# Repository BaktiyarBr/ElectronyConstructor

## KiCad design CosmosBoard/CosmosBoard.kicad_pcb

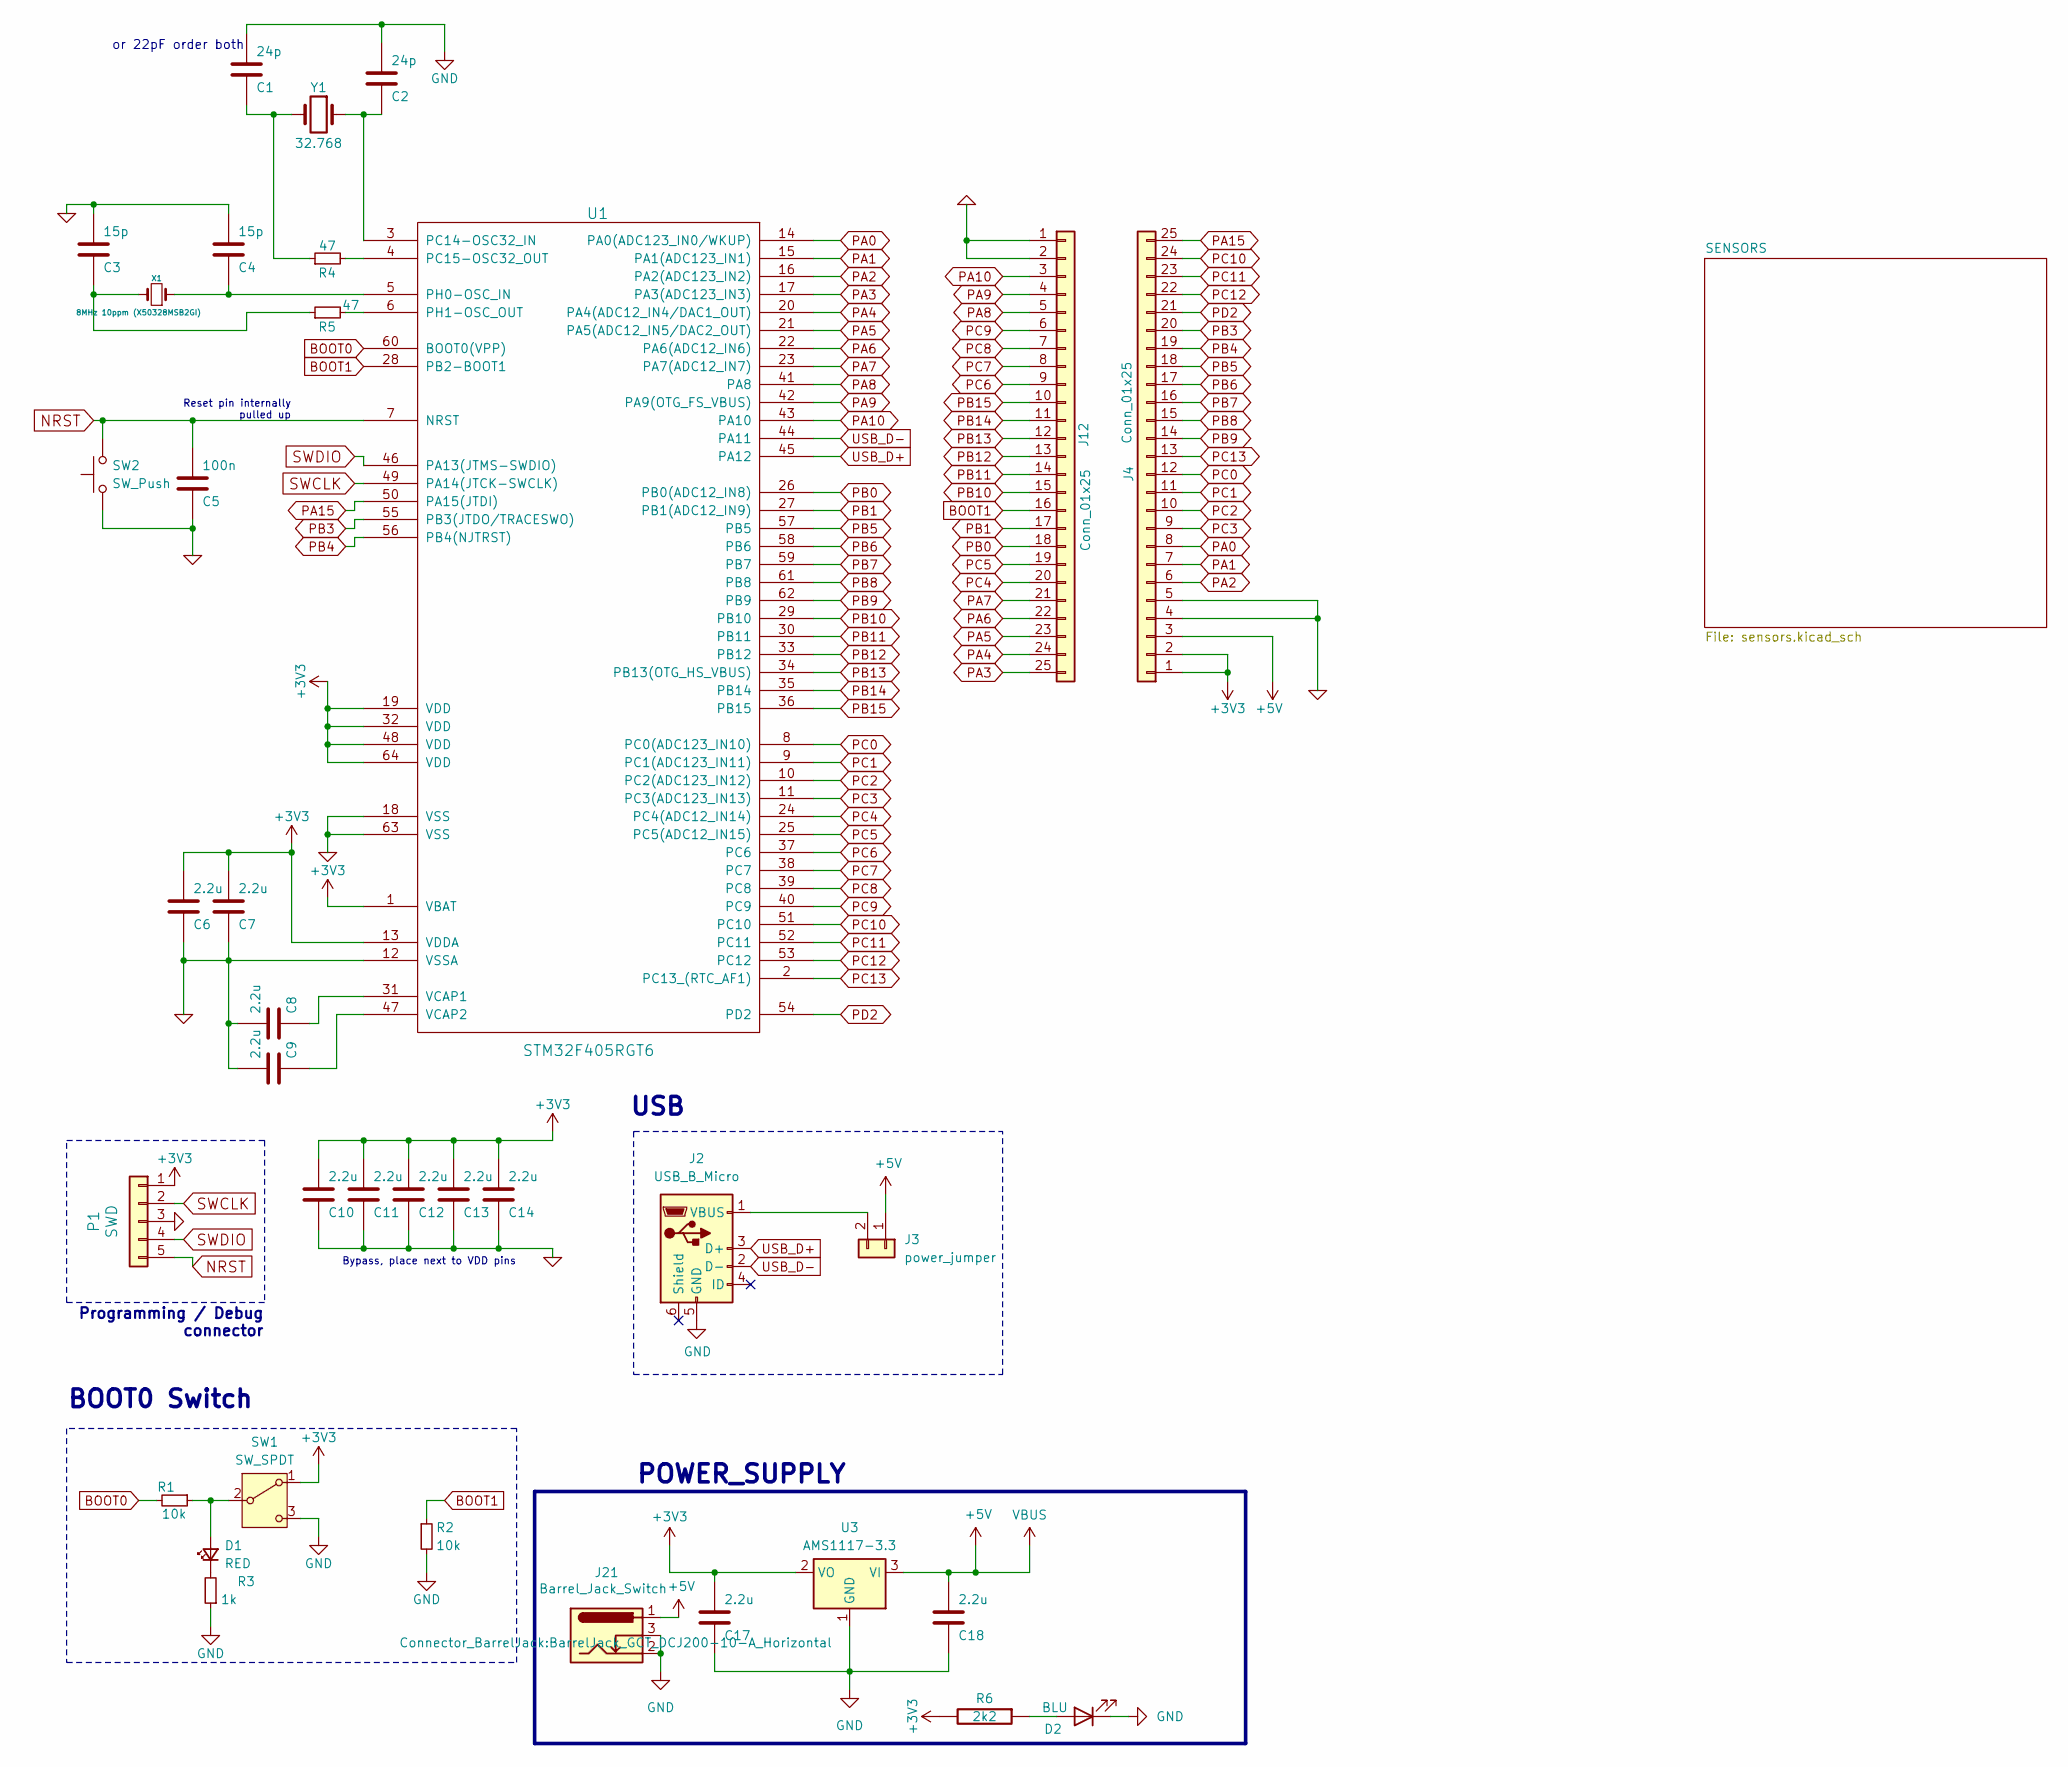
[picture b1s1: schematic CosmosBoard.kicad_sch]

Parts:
C1, C2: 24p; C_0603_1608Metric
C3, C4: 15p; C_0603_1608Metric
C5: 100n; C_0603_1608Metric
C6, C7, C8, C9, C10, C11, C12, C13, C14, C17, C18: 2.2u; C_0603_1608Metric
D1: RED; LED_0603_1608Metric; LCSC Part # C2286
D2: BLU; LED_0603_1608Metric
J2: USB_B_Micro; USB_Mini-B_Lumberg_2486_01_Horizontal
J3: power_jumper; PinHeader_1x02_P2.54mm_Vertical
J4, J12: Conn_01x25; PinHeader_1x25_P2.54mm_Vertical
J21: Barrel_Jack_Switch; BarrelJack_GCT_DCJ200-10-A_Horizontal
P1: SWD; PinHeader_1x05_P2.54mm_Vertical
R1, R2: 10k; R_0603_1608Metric_Pad0.98x0.95mm_HandSolder; LCSC Part # C25744
R3: 1k; R_0603_1608Metric_Pad0.98x0.95mm_HandSolder; LCSC Part # C21190
R4, R5: 47; R_0603_1608Metric_Pad0.98x0.95mm_HandSolder; LCSC Part # C25118
R6: 2k2; R_0603_1608Metric_Pad0.98x0.95mm_HandSolder
SW1: SW_SPDT; SW_SPDT_PCM12
SW2: SW_Push; SW_Push_SPST_NO_Alps_SKRK
U1: STM32F405RGT6; LQFP-64_10x10mm_P0.5mm
U3: AMS1117-3.3; SOT-223-3_TabPin2
X1: 8MHz 10ppm (X50328MSB2GI); Crystal_SMD_5032-2Pin_5.0x3.2mm; mfg# ABM3B-8.0-10-1UT
Y1: 32.768; Crystal_SMD_3215-2Pin_3.2x1.5mm

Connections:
+3V3: C6.2, C7.2, C10.2, C11.2, C12.2, C13.2, C14.2, C17.2, J4.1, J4.2, P1.1, R6.2, SW1.1 (A), U1.1 (VBAT), U1.13 (VDDA), U1.19 (VDD), U1.32 (VDD), U1.48 (VDD), U1.64 (VDD), U3.2 (VO); also elsewhere on the board
+5V: C18.2, J3.1, J4.3, J21.1, U3.3 (VI); also elsewhere on the board
BOOT0: R1.2, U1.60 (BOOT0(VPP))
BOOT1: J12.16, R2.1, U1.28 (PB2-BOOT1)
GND: C1.2, C2.2, C3.2, C4.2, C5.1, C6.1, C7.1, C8.2, C9.2, C10.1, C11.1, C12.1, C13.1, C14.1, C17.1, C18.1, D2.1 (K), J2.5 (GND), J4.4, J4.5, J12.1, J12.2, J21.2, J21.3, P1.3, R2.2, R3.1, SW1.3 (C), SW2.1, U1.12 (VSSA), U1.18 (VSS), U1.63 (VSS), U3.1 (GND); also elsewhere on the board
NRST: C5.2, P1.5, SW2.2, U1.7 (NRST)
unnamed: C1.1, R4.1, Y1.2
unnamed: C3.1, R5.1, X1.2
unnamed: D1.2 (A), R1.1, SW1.2 (B)
unnamed: D1.1 (K), R3.2
unnamed: D2.2 (A), R6.1
unnamed: J2.1 (VBUS), J3.2
unnamed: C2.1, U1.3 (PC14-OSC32_IN), Y1.1
unnamed: R4.2, U1.4 (PC15-OSC32_OUT)
unnamed: C4.1, U1.5 (PH0-OSC_IN), X1.1
unnamed: R5.2, U1.6 (PH1-OSC_OUT)
unnamed: C8.1, U1.31 (VCAP1)
unnamed: C9.1, U1.47 (VCAP2)
PA0: J4.8, U1.14 (PA0(ADC123_IN0/WKUP))
PA1: J4.7, U1.15 (PA1(ADC123_IN1))
PA2: J4.6, U1.16 (PA2(ADC123_IN2))
PA3: J12.25, U1.17 (PA3(ADC123_IN3))
PA4: J12.24, U1.20 (PA4(ADC12_IN4/DAC1_OUT))
PA5: J12.23, U1.21 (PA5(ADC12_IN5/DAC2_OUT))
PA6: J12.22, U1.22 (PA6(ADC12_IN6))
PA7: J12.21, U1.23 (PA7(ADC12_IN7))
PA8: J12.5, U1.41 (PA8)
PA9: J12.4, U1.42 (PA9(OTG_FS_VBUS))
PA10: J12.3, U1.43 (PA10)
PA15: J4.25, U1.50 (PA15(JTDI))
PB0: J12.18, U1.26 (PB0(ADC12_IN8))
PB1: J12.17, U1.27 (PB1(ADC12_IN9))
PB3: J4.20, U1.55 (PB3(JTDO/TRACESWO))
PB4: J4.19, U1.56 (PB4(NJTRST))
PB5: J4.18, U1.57 (PB5)
PB6: J4.17, U1.58 (PB6)
PB7: J4.16, U1.59 (PB7)
PB8: J4.15, U1.61 (PB8)
PB9: J4.14, U1.62 (PB9)
PB10: J12.15, U1.29 (PB10)
PB11: J12.14, U1.30 (PB11)
PB12: J12.13, U1.33 (PB12)
PB13: J12.12, U1.34 (PB13(OTG_HS_VBUS))
PB14: J12.11, U1.35 (PB14)
PB15: J12.10, U1.36 (PB15)
PC0: J4.12, U1.8 (PC0(ADC123_IN10))
PC1: J4.11, U1.9 (PC1(ADC123_IN11))
PC2: J4.10, U1.10 (PC2(ADC123_IN12))
PC3: J4.9, U1.11 (PC3(ADC123_IN13))
PC4: J12.20, U1.24 (PC4(ADC12_IN14))
PC5: J12.19, U1.25 (PC5(ADC12_IN15))
PC6: J12.9, U1.37 (PC6)
PC7: J12.8, U1.38 (PC7)
PC8: J12.7, U1.39 (PC8)
PC9: J12.6, U1.40 (PC9)
PC10: J4.24, U1.51 (PC10)
PC11: J4.23, U1.52 (PC11)
PC12: J4.22, U1.53 (PC12)
PC13: J4.13, U1.2 (PC13_(RTC_AF1))
PD2: J4.21, U1.54 (PD2)
SWCLK: P1.2, U1.49 (PA14(JTCK-SWCLK))
SWDIO: P1.4, U1.46 (PA13(JTMS-SWDIO))
USB_D+: J2.3 (D+), U1.45 (PA12)
USB_D-: J2.2 (D-), U1.44 (PA11)

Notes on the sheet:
USB
POWER_SUPPLY
BOOT0 Switch
Reset pin internally pulled up
Programming / Debug connector
Bypass, place next to VDD pins
or 22pF order both

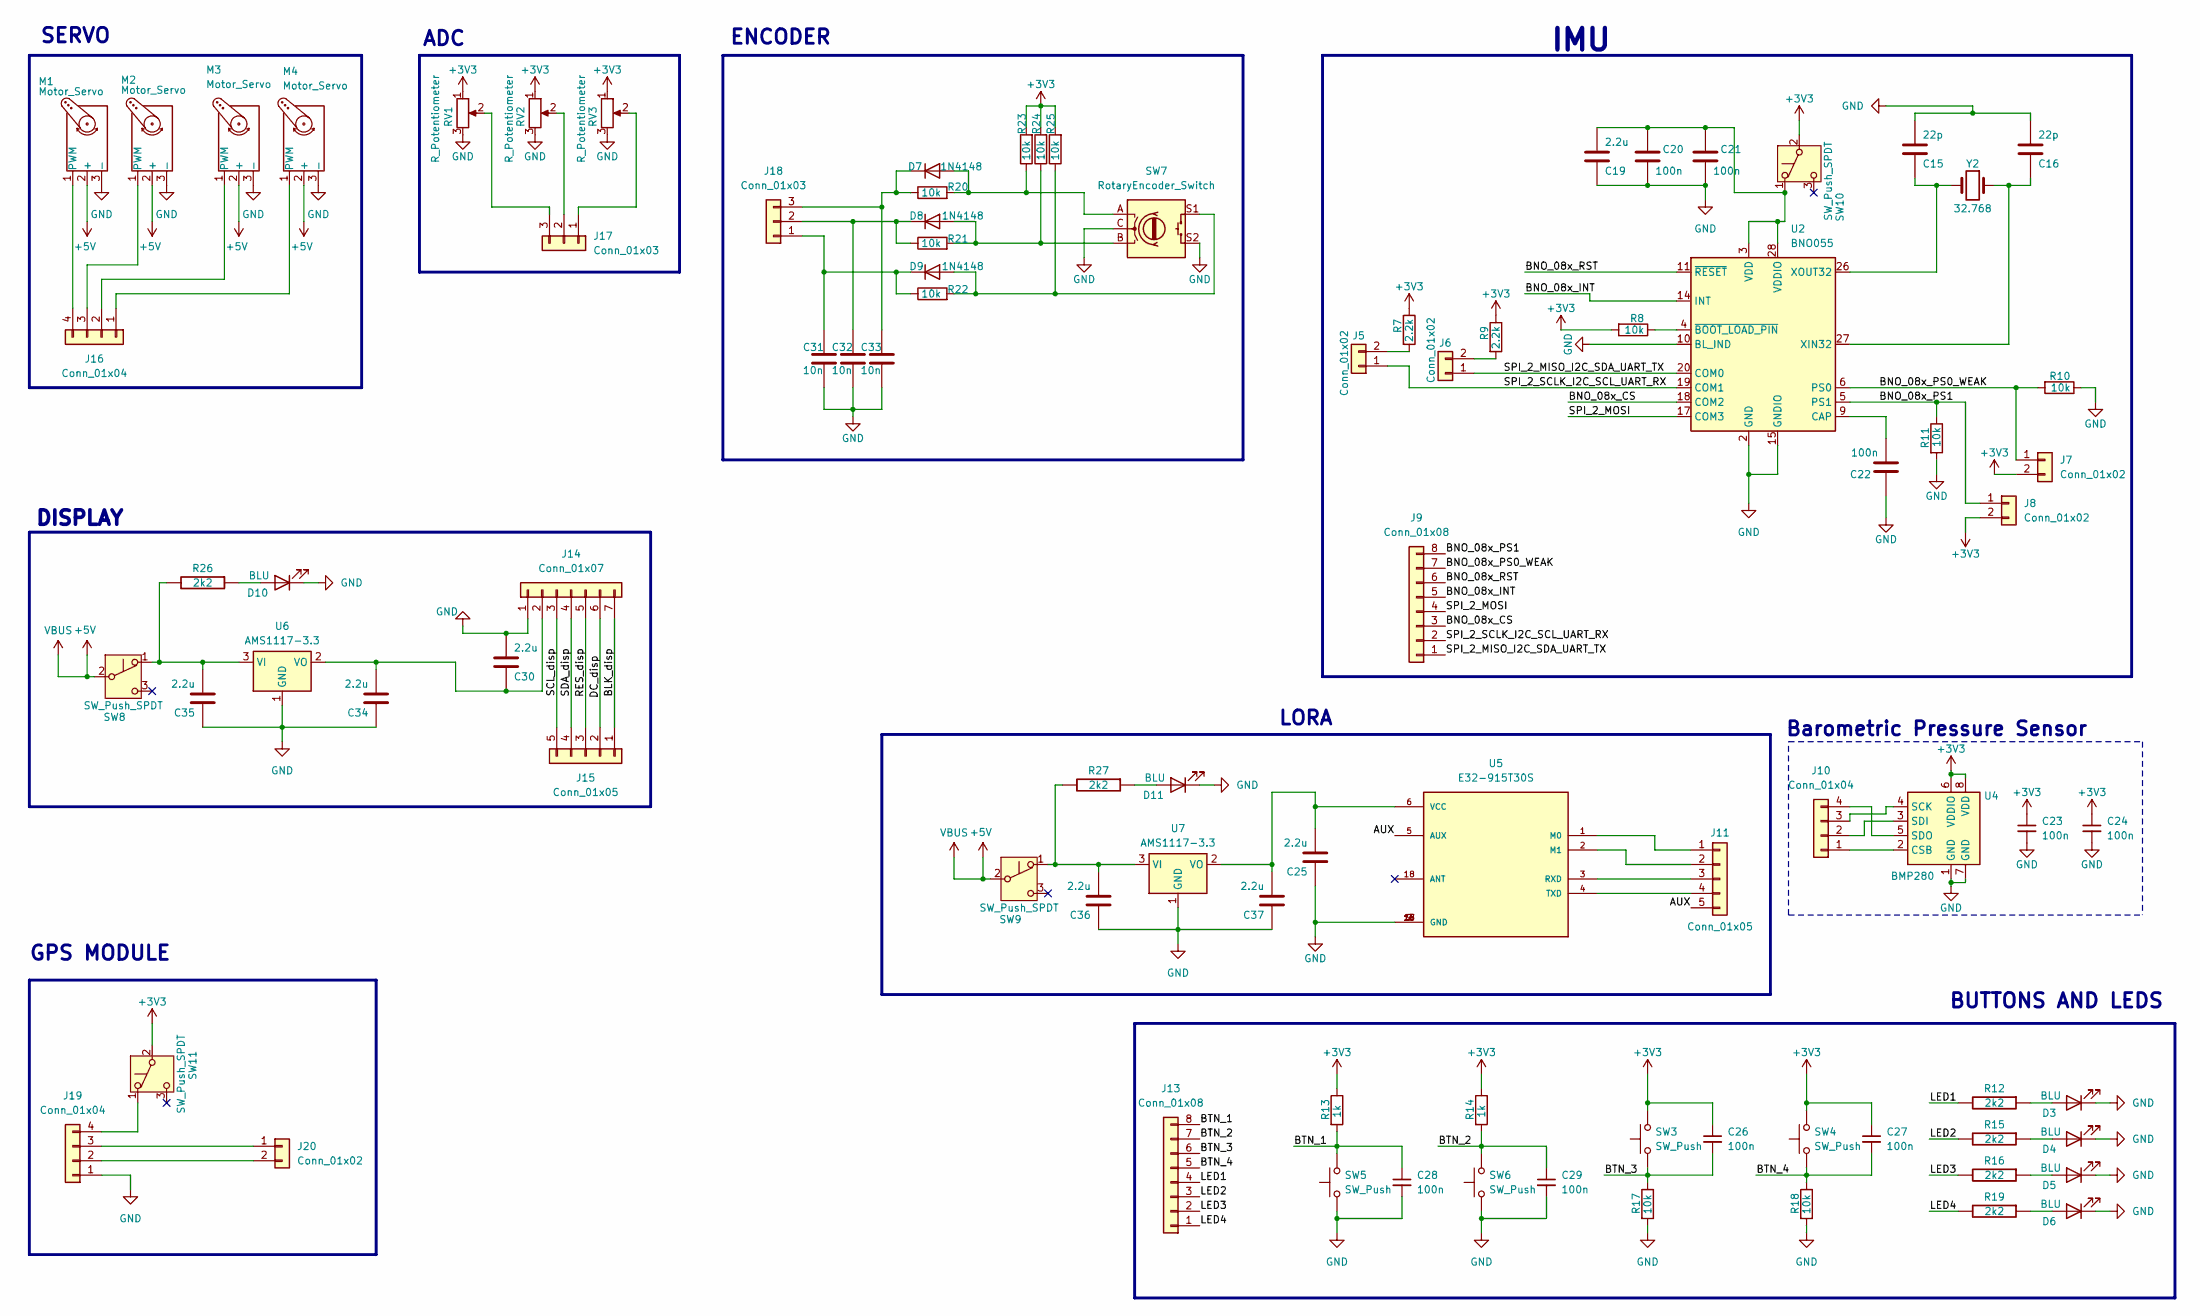
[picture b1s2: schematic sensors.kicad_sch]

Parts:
C15, C16: 22p; C_0603_1608Metric
C19, C25, C30, C34, C35, C36, C37: 2.2u; C_0603_1608Metric
C20, C21, C22: 100n; C_0603_1608Metric
C23, C24: 100n; C_0402_1005Metric; LCSC Part # C1525
C26, C27, C28, C29: 100n; C_0603_1608Metric; LCSC Part # C1525
C31, C32, C33: 10n; C_0603_1608Metric
D3, D4, D5, D6, D10, D11: BLU; LED_0603_1608Metric
D7, D8, D9: 1N4148; D_DO-35_SOD27_P7.62mm_Horizontal
J5, J6, J7, J8, J20: Conn_01x02; PinHeader_1x02_P2.54mm_Vertical
J9, J13: Conn_01x08; PinHeader_1x08_P2.54mm_Vertical
J10, J16, J19: Conn_01x04; PinHeader_1x04_P2.54mm_Vertical
J11, J15: Conn_01x05; PinHeader_1x05_P2.54mm_Vertical
J14: Conn_01x07; PinHeader_1x07_P2.54mm_Vertical
J17, J18: Conn_01x03; PinHeader_1x03_P2.54mm_Vertical
M1, M2, M3, M4: Motor_Servo; PinHeader_1x03_P2.54mm_Vertical
R7, R9: 2.2k; R_0603_1608Metric_Pad0.98x0.95mm_HandSolder
R8, R10, R11, R17, R18, R20, R21, R22, R23, R24, R25: 10k; R_0603_1608Metric_Pad0.98x0.95mm_HandSolder
R12, R15, R16, R19, R26, R27: 2k2; R_0603_1608Metric_Pad0.98x0.95mm_HandSolder
R13, R14: 1k; R_0603_1608Metric_Pad0.98x0.95mm_HandSolder
RV1, RV2, RV3: R_Potentiometer; Potentiometer_TT_P0915N
SW3, SW4, SW5, SW6: SW_Push; SW_PUSH-12mm
SW7: RotaryEncoder_Switch; RotaryEncoder_Alps_EC11E-Switch_Vertical_H20mm_CircularMoun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
SW8, SW9, SW10, SW11: SW_Push_SPDT; SW_Slide-03_Wuerth-WS-SLTV_10x2.5x6.4_P2.54mm
U2: BNO055; LGA-28_5.2x3.8mm_P0.5mm
U4: BMP280; Bosch_LGA-8_2x2.5mm_P0.65mm_ClockwisePinNumbering; LCSC Part # C233787
U5: E32-915T30S; XCVR_E22-900T30S; PARTREV 1.4
U6, U7: AMS1117-3.3; SOT-223-3_TabPin2
Y2: 32.768; Crystal_SMD_3215-2Pin_3.2x1.5mm

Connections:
+3V3: C23.1, C24.1, C26.1, C27.1, J7.2, J8.2, R7.1, R8.2, R9.1, R13.1, R14.1, R23.2, R24.2, R25.2, RV1.1, RV2.1, RV3.1, SW3.2, SW4.2, SW10.2 (B), SW11.2 (B), U4.6 (VDDIO), U4.8 (VDD); also elsewhere on the board
+5V: M1.2 (+), M2.2 (+), M3.2 (+), M4.2 (+), SW8.2 (B), SW9.2 (B); also elsewhere on the board
/SENSORS/AUX: J11.5, U5.5 (AUX)
/SENSORS/BLK_disp: J14.7, J15.1
/SENSORS/BNO_08x_CS: J9.3, U2.18 (COM2)
/SENSORS/BNO_08x_INT: J9.5, U2.14 (INT)
/SENSORS/BNO_08x_PS0_WEAK: J7.1, J9.7, R10.2, U2.6 (PS0)
/SENSORS/BNO_08x_PS1: J8.1, J9.8, R11.1, U2.5 (PS1)
/SENSORS/BNO_08x_RST: J9.6, U2.11 (~RESET)
/SENSORS/BTN_1: C28.1, J13.8, R13.2, SW5.2
/SENSORS/BTN_2: C29.1, J13.7, R14.2, SW6.2
/SENSORS/BTN_3: C26.2, J13.6, R17.1, SW3.1
/SENSORS/BTN_4: C27.2, J13.5, R18.1, SW4.1
/SENSORS/DC_disp: J14.6, J15.2
/SENSORS/LED1: J13.4, R12.2
/SENSORS/LED2: J13.3, R15.2
/SENSORS/LED3: J13.2, R16.2
/SENSORS/LED4: J13.1, R19.2
/SENSORS/RES_disp: J14.5, J15.3
/SENSORS/SCL_disp: J14.3, J15.5
/SENSORS/SDA_disp: J14.4, J15.4
/SENSORS/SPI_2_MISO_I2C_SDA_UART_TX: J6.1, J9.1, U2.20 (COM0)
/SENSORS/SPI_2_MOSI: J9.4, U2.17 (COM3)
/SENSORS/SPI_2_SCLK_I2C_SCL_UART_RX: J5.1, J9.2, U2.19 (COM1)
GND: C15.2, C16.2, C19.1, C20.2, C21.2, C22.1, C23.2, C24.2, C25.1, C28.2, C29.2, C30.2, C31.2, C32.2, C33.2, C34.1, C35.1, C36.1, C37.1, D3.1 (K), D4.1 (K), D5.1 (K), D6.1 (K), D10.1 (K), D11.1 (K), J14.1, J19.1, M1.3 (-), M2.3 (-), M3.3 (-), M4.3 (-), R10.1, R11.2, R17.2, R18.2, RV1.3, RV2.3, RV3.3, SW5.1, SW6.1, SW7.C, SW7.S2, U2.2 (GND), U2.10 (BL_IND), U2.15 (GNDIO), U2.16 (GNDIO), U2.25 (GNDIO), U4.1 (GND), U4.7 (GND), U5.7 (GND), U5.9 (GND), U5.15 (GND), U5.16 (GND), U5.17 (GND), U6.1 (GND), U7.1 (GND); also elsewhere on the board
unnamed: D3.2 (A), R12.1
unnamed: D4.2 (A), R15.1
unnamed: D5.2 (A), R16.1
unnamed: D6.2 (A), R19.1
unnamed: D7.2 (A), R20.2, R23.1, SW7.A
unnamed: C33.1, D7.1 (K), J18.3, R20.1
unnamed: D8.2 (A), R21.2, R24.1, SW7.B
unnamed: C32.1, D8.1 (K), J18.2, R21.1
unnamed: D9.2 (A), R22.2, R25.1, SW7.S1
unnamed: C31.1, D9.1 (K), J18.1, R22.1
unnamed: D10.2 (A), R26.1
unnamed: D11.2 (A), R27.1
unnamed: J5.2, R7.2
unnamed: J6.2, R9.2
unnamed: J10.1, U4.2 (CSB)
unnamed: J10.2, U4.3 (SDI)
unnamed: J10.3, U4.4 (SCK)
unnamed: J10.4, U4.5 (SDO)
unnamed: J11.1, U5.1 (M0)
unnamed: J11.2, U5.2 (M1)
unnamed: J11.3, U5.3 (RXD)
unnamed: J11.4, U5.4 (TXD)
unnamed: C30.1, C34.2, J14.2, U6.2 (VO)
unnamed: J16.1, M4.1 (PWM)
unnamed: J16.2, M3.1 (PWM)
unnamed: J16.3, M2.1 (PWM)
unnamed: J16.4, M1.1 (PWM)
unnamed: J17.1, RV3.2
unnamed: J17.2, RV2.2
unnamed: J17.3, RV1.2
unnamed: J19.2, J20.2
unnamed: J19.3, J20.1
unnamed: J19.4, SW11.1 (A)
unnamed: C35.2, R26.2, SW8.1 (A), U6.3 (VI)
unnamed: C36.2, R27.2, SW9.1 (A), U7.3 (VI)
unnamed: C19.2, C20.1, C21.1, SW10.1 (A), U2.3 (VDD), U2.28 (VDDIO)
unnamed: C22.2, U2.9 (CAP)
unnamed: C16.1, U2.27 (XIN32), Y2.1
unnamed: C15.1, U2.26 (XOUT32), Y2.2
unnamed: R8.1, U2.4 (~BOOT_LOAD_PIN)
unnamed: C25.2, C37.2, U5.6 (VCC), U7.2 (VO)

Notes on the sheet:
GPS MODULE
DISPLAY
Barometric Pressure Sensor
IMU
ADC
SERVO
BUTTONS AND LEDS
ENCODER
LORA

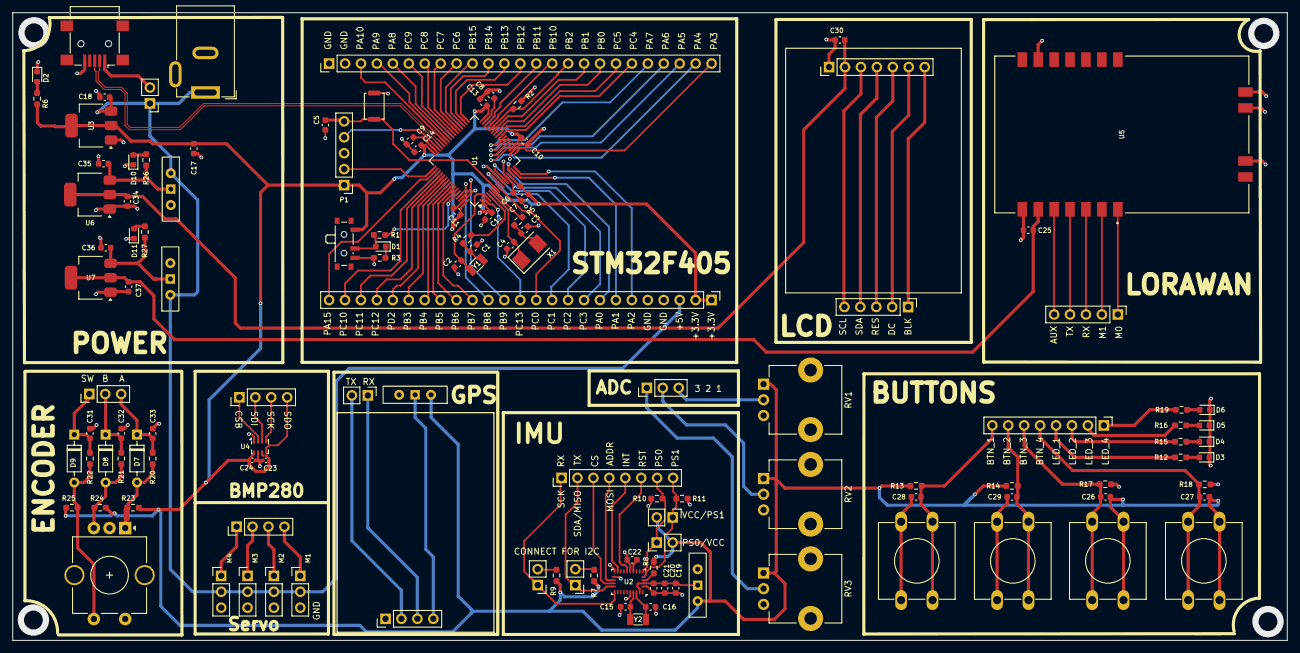
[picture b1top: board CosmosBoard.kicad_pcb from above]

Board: 4 copper layers, 203.2 x 100.0 mm, 124 parts (0 on the bottom side), 127 nets.

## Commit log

2024-06-26 alligns
2024-06-27 traces
2024-06-27 box for bno
2024-06-29 pre-final
